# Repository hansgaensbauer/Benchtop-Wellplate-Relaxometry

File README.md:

# Benchtop Wellplate Relaxometry Hardware

Hardware for the system described in "Rapid Parallel Magnetic Resonance Relaxometry on Multiwell Plates with a Benchtop Scanner", by Hans Gaensbauer, Yanmeng Yang, Daniel Roxby, David Bono, and Jongyoon Han.

Also see the 96wp branch of [the MR-Core Repo](https://github.com/hansgaensbauer/MR-Core).

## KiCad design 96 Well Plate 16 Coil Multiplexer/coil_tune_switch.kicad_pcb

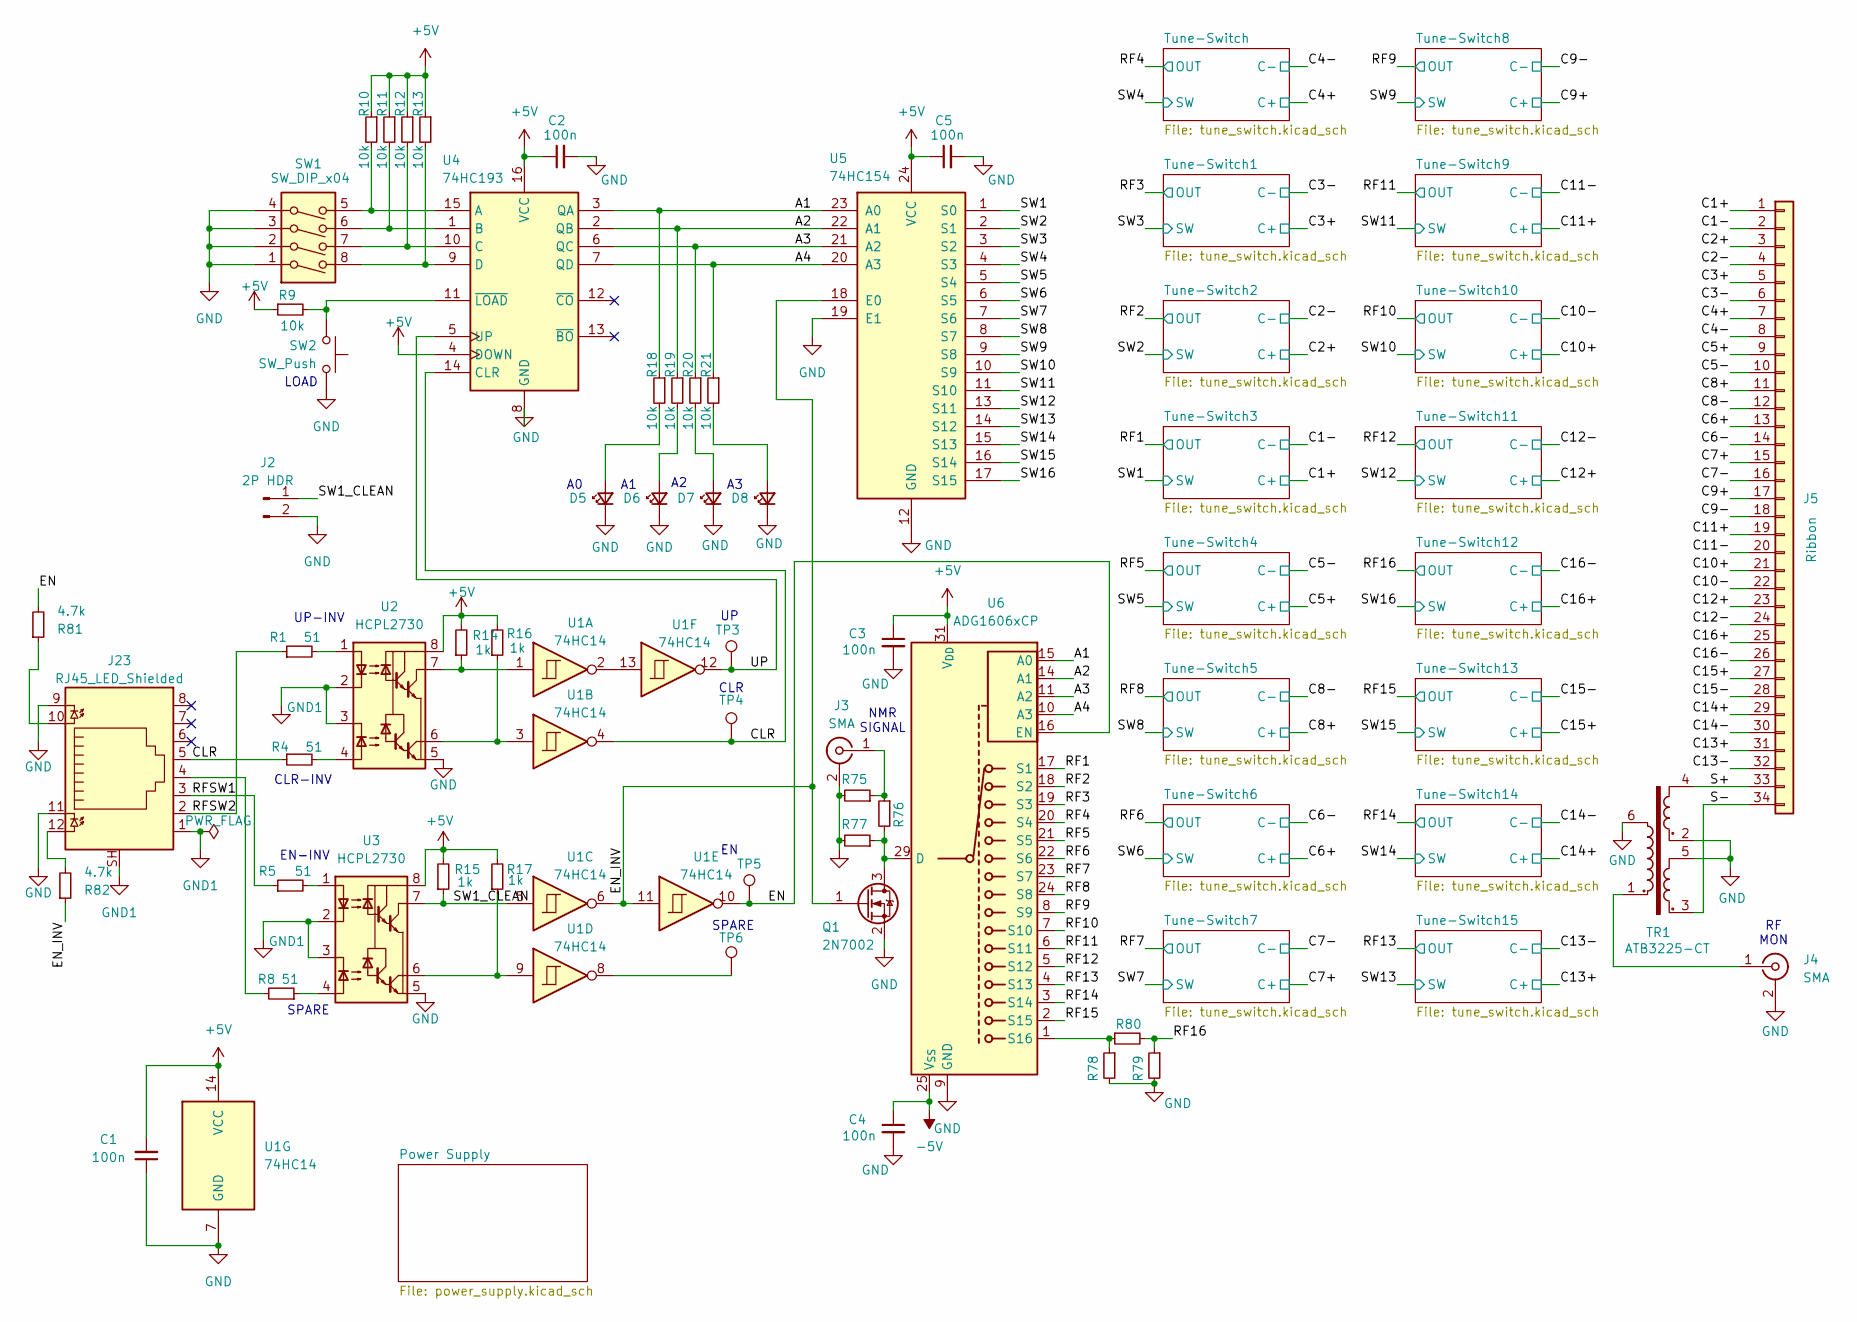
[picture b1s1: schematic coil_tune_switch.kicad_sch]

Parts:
C1, C2, C3, C4, C5: 100n; C_0603_1608Metric
D5, D6, D7, D8: LED_Small; LED_0603_1608Metric
J2: 2P HDR; PinHeader_1x02_P2.54mm_Vertical
J3, J4: SMA; SMA_Samtec_SMA-J-P-H-ST-EM1_EdgeMount
J5: Ribbon; IDC-Header_2x17_P2.54mm_Latch_Horizontal
J23: RJ45_LED_Shielded; RJ45_Amphenol_RJHSE538X
Q1: 2N7002; SOT-23
R1, R4, R5, R8: 51; R_0603_1608Metric
R9, R10, R11, R12, R13, R18, R19, R20, R21: 10k; R_0603_1608Metric
R14, R15, R16, R17, R75, R76, R77, R78, R79, R80: 1k; R_0603_1608Metric
R81, R82: 4.7k; R_0603_1608Metric
SW1: SW_DIP_x04; SW_DIP_SPSTx04_Slide_Omron_A6S-410x_W8.9mm_P2.54mm
SW2: SW_Push; SW_SPST_Omron_B3FS-100xP
TP3, TP4, TP5: TestPoint; TestPoint_Bridge_Pitch2.0mm_Drill0.7mm
TP6: TestPoint; TestPoint_THTPad_D1.0mm_Drill0.5mm
TR1: ATB3225-CT; ATB3225
U1: 74HC14; SOIC-14_3.9x8.7mm_P1.27mm
U2, U3: HCPL2730; SMDIP-8_W9.53mm
U4: 74HC193; SOIC-16_3.9x9.9mm_P1.27mm
U5: 74HC154; SOIC-24W_7.5x15.4mm_P1.27mm
U6: ADG1606xCP; LFCSP-32-1EP_5x5mm_P0.5mm_EP3.1x3.1mm

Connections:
+5V: C1.2, C2.1, C3.1, C5.1, R9.1, R10.1, R11.1, R12.1, R13.1, R14.2, R15.2, R16.2, R17.2, U1.14 (VCC), U2.8 (VCC), U3.8 (VCC), U4.4 (DOWN), U4.16 (VCC), U5.24 (VCC), U6.31 (V_{DD}); also elsewhere on the board
-5V: C4.1, U6.25 (V_{SS}), U6.33 (V_{SS}); also elsewhere on the board
/A1: R18.1, U4.3 (QA), U5.23 (A0), U6.15 (A0)
/A2: R19.1, U4.2 (QB), U5.22 (A1), U6.14 (A1)
/A3: R20.1, U4.6 (QC), U5.21 (A2), U6.11 (A2)
/A4: R21.1, U4.7 (QD), U5.20 (A3), U6.10 (A3)
/C1+: J5.1; also elsewhere on the board
/C1-: J5.2; also elsewhere on the board
/C2+: J5.3; also elsewhere on the board
/C2-: J5.4; also elsewhere on the board
/C3+: J5.5; also elsewhere on the board
/C3-: J5.6; also elsewhere on the board
/C4+: J5.7; also elsewhere on the board
/C4-: J5.8; also elsewhere on the board
/C5+: J5.9; also elsewhere on the board
/C5-: J5.10; also elsewhere on the board
/C6+: J5.13; also elsewhere on the board
/C6-: J5.14; also elsewhere on the board
/C7+: J5.15; also elsewhere on the board
/C7-: J5.16; also elsewhere on the board
/C8+: J5.11; also elsewhere on the board
/C8-: J5.12; also elsewhere on the board
/C9+: J5.17; also elsewhere on the board
/C9-: J5.18; also elsewhere on the board
/C10+: J5.21; also elsewhere on the board
/C10-: J5.22; also elsewhere on the board
/C11+: J5.19; also elsewhere on the board
/C11-: J5.20; also elsewhere on the board
/C12+: J5.23; also elsewhere on the board
/C12-: J5.24; also elsewhere on the board
/C13+: J5.31; also elsewhere on the board
/C13-: J5.32; also elsewhere on the board
/C14+: J5.29; also elsewhere on the board
/C14-: J5.30; also elsewhere on the board
/C15+: J5.27; also elsewhere on the board
/C15-: J5.28; also elsewhere on the board
/C16+: J5.25; also elsewhere on the board
/C16-: J5.26; also elsewhere on the board
/CLR: J23.5, R4.1, TP4.1, U1.4, U4.14 (CLR)
/EN: R81.2, TP5.1, U1.10, U6.16 (EN)
/EN_INV: Q1.1 (G), R82.1, U1.6, U1.11, U5.18 (E0)
/RF1: U6.17 (S1); also elsewhere on the board
/RF2: U6.18 (S2); also elsewhere on the board
/RF3: U6.19 (S3); also elsewhere on the board
/RF4: U6.20 (S4); also elsewhere on the board
/RF5: U6.21 (S5); also elsewhere on the board
/RF6: U6.22 (S6); also elsewhere on the board
/RF7: U6.23 (S7); also elsewhere on the board
/RF8: U6.24 (S8); also elsewhere on the board
/RF9: U6.8 (S9); also elsewhere on the board
/RF10: U6.7 (S10); also elsewhere on the board
/RF11: U6.6 (S11); also elsewhere on the board
/RF12: U6.5 (S12); also elsewhere on the board
/RF13: U6.4 (S13); also elsewhere on the board
/RF14: U6.3 (S14); also elsewhere on the board
/RF15: U6.2 (S15); also elsewhere on the board
/RF16: R79.1, R80.2; also elsewhere on the board
/RFSW1: J23.3, R5.1
/RFSW2: J23.2, R1.1
/S+: J5.33, TR1.4
/S-: J5.34, TR1.3
/SW1: U5.1 (S0); also elsewhere on the board
/SW1_CLEAN: J2.1, R15.1, U1.5, U3.7 (VO1)
/SW2: U5.2 (S1); also elsewhere on the board
/SW3: U5.3 (S2); also elsewhere on the board
/SW4: U5.4 (S3); also elsewhere on the board
/SW5: U5.5 (S4); also elsewhere on the board
/SW6: U5.6 (S5); also elsewhere on the board
/SW7: U5.7 (S6); also elsewhere on the board
/SW8: U5.8 (S7); also elsewhere on the board
/SW9: U5.9 (S8); also elsewhere on the board
/SW10: U5.10 (S9); also elsewhere on the board
/SW11: U5.11 (S10); also elsewhere on the board
/SW12: U5.13 (S11); also elsewhere on the board
/SW13: U5.14 (S12); also elsewhere on the board
/SW14: U5.15 (S13); also elsewhere on the board
/SW15: U5.16 (S14); also elsewhere on the board
/SW16: U5.17 (S15); also elsewhere on the board
/UP: TP3.1, U1.12, U4.5 (UP)
GND: C1.1, C2.2, C3.2, C4.2, C5.2, D5.1 (K), D6.1 (K), D7.1 (K), D8.1 (K), J2.2, J3.2 (Ext), J4.2 (Ext), J23.9, J23.11, Q1.2 (S), R75.2, R77.2, R78.2, R79.2, SW1.1, SW1.2, SW1.3, SW1.4, SW2.1, TR1.2, TR1.5, TR1.6, U1.7 (GND), U2.5 (GND), U3.5 (GND), U4.8 (GND), U5.12 (GND), U5.19 (E1), U6.9 (GND); also elsewhere on the board
GND1: J23.1, J23.SH, U2.2 (C1), U2.3 (C2), U3.2 (C1), U3.3 (C2)
unnamed: D5.2 (A), R18.2
unnamed: D6.2 (A), R19.2
unnamed: D7.2 (A), R20.2
unnamed: D8.2 (A), R21.2
unnamed: J3.1 (In), R75.1, R76.1
unnamed: J4.1 (In), TR1.1
unnamed: J23.4, R8.2
unnamed: J23.10, R81.1
unnamed: J23.12, R82.2
unnamed: Q1.3 (D), R76.2, R77.1, U6.29 (D)
unnamed: TP6.1, U1.8
unnamed: U1.2, U1.13
unnamed: R1.2, U2.1 (A1)
unnamed: R4.2, U2.4 (A2)
unnamed: R14.1, U1.1, U2.7 (VO1)
unnamed: R16.1, U1.3, U2.6 (VO2)
unnamed: R5.2, U3.1 (A1)
unnamed: R8.1, U3.4 (A2)
unnamed: R17.1, U1.9, U3.6 (VO2)
unnamed: R10.2, SW1.5, U4.15 (A)
unnamed: R11.2, SW1.6, U4.1 (B)
unnamed: R12.2, SW1.7, U4.10 (C)
unnamed: R13.2, SW1.8, U4.9 (D)
unnamed: R9.2, SW2.2, U4.11 (~LOAD)
unnamed: R78.1, R80.1, U6.1 (S16)

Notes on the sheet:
UP-INV
NMR SIGNAL
RF MON
CLR-INV
EN-INV
SPARE
CLR
LOAD

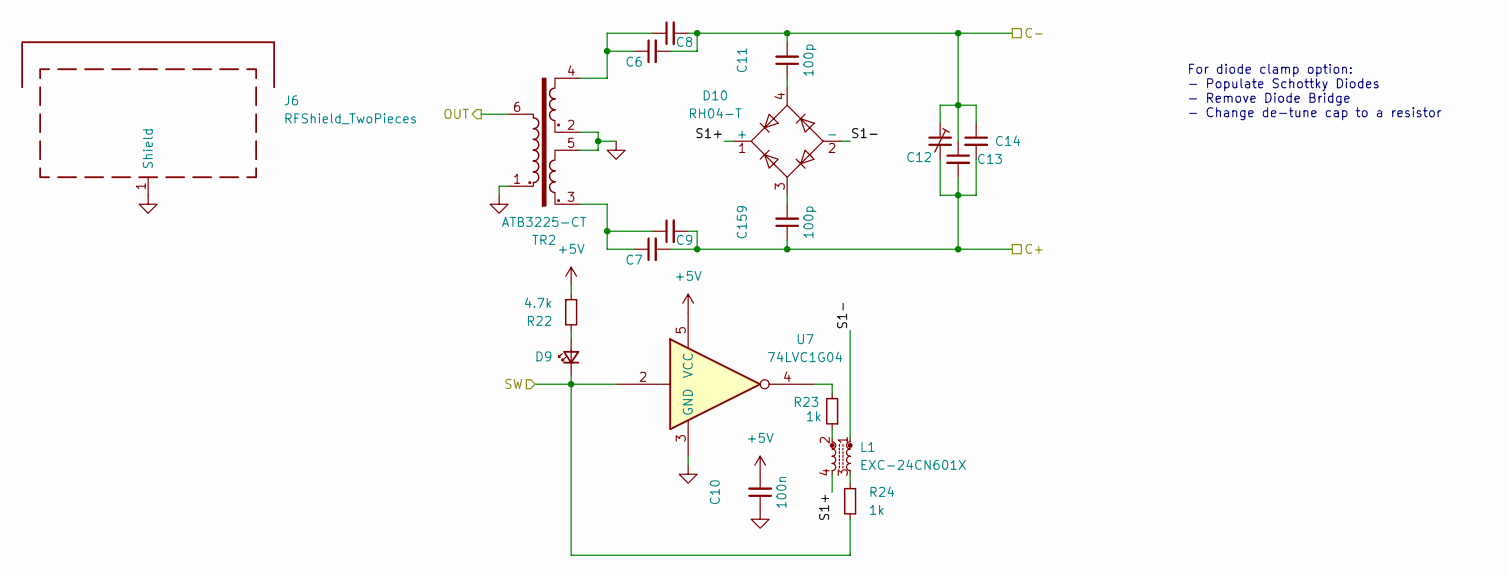
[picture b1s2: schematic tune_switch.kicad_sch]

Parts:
C6, C7, C8, C9, C13, C14: C_Small; C_0603_1608Metric
C10: 100n; C_0603_1608Metric
C11, C159: 100p; C_0603_1608Metric
C12: C_Trim_Small; C_Trimmer_Voltronics_JZ
D9: LED_Small; LED_0603_1608Metric
D10: RH04-T; MiniDIP-4
J6: RFShield_TwoPieces; Laird_Technologies_BMI-S-202-F_16.50x16.50mm
L1: EXC-24CN601X
R22: 4.7k; R_0603_1608Metric
R23, R24: 1k; R_0603_1608Metric
TR2: ATB3225-CT; ATB3225
U7: 74LVC1G04; SOT-353_SC-70-5

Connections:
+5V: C10.2, R22.1, U7.5 (VCC); also elsewhere on the board
/C4+: C7.2, C9.2, C12.2, C13.2, C14.2, C159.1; also elsewhere on the board
/C4-: C6.2, C8.2, C11.2, C12.1, C13.1, C14.1; also elsewhere on the board
/RF4: TR2.6; also elsewhere on the board
/SW4: D9.1 (K), R24.1, U7.2; also elsewhere on the board
/Tune-Switch/S1+: D10.1 (+), L1.4
/Tune-Switch/S1-: D10.2 (-), L1.1
GND: C10.1, J6.1 (Shield), TR2.1, TR2.2, TR2.5, U7.3 (GND); also elsewhere on the board
unnamed: C6.1, C8.1, TR2.4
unnamed: C7.1, C9.1, TR2.3
unnamed: C11.1, D10.4
unnamed: C159.2, D10.3
unnamed: D9.2 (A), R22.2
unnamed: L1.2, R23.1
unnamed: L1.3, R24.2
unnamed: R23.2, U7.4

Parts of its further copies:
C15, C16, C17, C18, C22, C23, C24, C25, C26, C27, C31, C32, C33, C34, C35, C36, C40, C41, C42, C43, C44, C45, C49, C50, C51, C52, C53, C54, C58, C59, C60, C61, C62, C63, C67, C68, C69, C70, C71, C72, C76, C77, C78, C79, C80, C81, C85, C86, C87, C88, C89, C90, C94, C95, C96, C97, C98, C99, C103, C104, C105, C106, C107, C108, C112, C113, C114, C115, C116, C117, C121, C122, C123, C124, C125, C126, C130, C131, C132, C133, C134, C135, C139, C140, C141, C142, C143, C144, C148, C149: C_Small; C_0603_1608Metric
C19, C28, C37, C46, C55, C64, C73, C82, C91, C100, C109, C118, C127, C136, C145: 100n; C_0603_1608Metric
C20, C29, C38, C47, C56, C65, C74, C83, C92, C101, C110, C119, C128, C137, C146, C160, C161, C162, C163, C164, C165, C166, C167, C168, C169, C170, C171, C172, C173, C174: 100p; C_0603_1608Metric
C21, C30, C39, C48, C57, C66, C75, C84, C93, C102, C111, C120, C129, C138, C147: C_Trim_Small; C_Trimmer_Voltronics_JZ
D13, D17, D21, D25, D29, D33, D37, D41, D45, D49, D53, D57, D61, D65, D69: LED_Small; LED_0603_1608Metric
D14, D18, D22, D26, D30, D34, D38, D42, D46, D50, D54, D58, D62, D66, D70: RH04-T; MiniDIP-4
J7, J8, J9, J10, J11, J12, J13, J14, J15, J16, J17, J18, J19, J20, J21: RFShield_TwoPieces; Laird_Technologies_BMI-S-202-F_16.50x16.50mm
L2, L3, L4, L5, L6, L7, L8, L9, L10, L11, L12, L13, L14, L15, L16: EXC-24CN601X
R25, R28, R31, R34, R37, R40, R43, R46, R49, R52, R55, R58, R61, R64, R67: 4.7k; R_0603_1608Metric
R26, R27, R29, R30, R32, R33, R35, R36, R38, R39, R41, R42, R44, R45, R47, R48, R50, R51, R53, R54, R56, R57, R59, R60, R62, R63, R65, R66, R68, R69: 1k; R_0603_1608Metric
TR3, TR4, TR5, TR6, TR7, TR8, TR9, TR10, TR11, TR12, TR13, TR14, TR15, TR16, TR17: ATB3225-CT; ATB3225
U8, U9, U10, U11, U12, U13, U14, U15, U16, U17, U18, U19, U20, U21, U22: 74LVC1G04; SOT-353_SC-70-5

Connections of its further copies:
+5V: C19.2, C28.2, C37.2, C46.2, C55.2, C64.2, C73.2, C82.2, C91.2, C100.2, C109.2, C118.2, C127.2, C136.2, C145.2, R25.1, R28.1, R31.1, R34.1, R37.1, R40.1, R43.1, R46.1, R49.1, R52.1, R55.1, R58.1, R61.1, R64.1, R67.1, U8.5 (VCC), U9.5 (VCC), U10.5 (VCC), U11.5 (VCC), U12.5 (VCC), U13.5 (VCC), U14.5 (VCC), U15.5 (VCC), U16.5 (VCC), U17.5 (VCC), U18.5 (VCC), U19.5 (VCC), U20.5 (VCC), U21.5 (VCC), U22.5 (VCC); also elsewhere on the board
/C1+: C34.2, C36.2, C39.2, C40.2, C41.2, C162.1; also elsewhere on the board
/C1-: C33.2, C35.2, C38.2, C39.1, C40.1, C41.1; also elsewhere on the board
/C2+: C25.2, C27.2, C30.2, C31.2, C32.2, C161.1; also elsewhere on the board
/C2-: C24.2, C26.2, C29.2, C30.1, C31.1, C32.1; also elsewhere on the board
/C3+: C16.2, C18.2, C21.2, C22.2, C23.2, C160.1; also elsewhere on the board
/C3-: C15.2, C17.2, C20.2, C21.1, C22.1, C23.1; also elsewhere on the board
/C5+: C43.2, C45.2, C48.2, C49.2, C50.2, C163.1; also elsewhere on the board
/C5-: C42.2, C44.2, C47.2, C48.1, C49.1, C50.1; also elsewhere on the board
/C6+: C61.2, C63.2, C66.2, C67.2, C68.2, C165.1; also elsewhere on the board
/C6-: C60.2, C62.2, C65.2, C66.1, C67.1, C68.1; also elsewhere on the board
/C7+: C70.2, C72.2, C75.2, C76.2, C77.2, C166.1; also elsewhere on the board
/C7-: C69.2, C71.2, C74.2, C75.1, C76.1, C77.1; also elsewhere on the board
/C8+: C52.2, C54.2, C57.2, C58.2, C59.2, C164.1; also elsewhere on the board
/C8-: C51.2, C53.2, C56.2, C57.1, C58.1, C59.1; also elsewhere on the board
/C9+: C79.2, C81.2, C84.2, C85.2, C86.2, C167.1; also elsewhere on the board
/C9-: C78.2, C80.2, C83.2, C84.1, C85.1, C86.1; also elsewhere on the board
/C10+: C97.2, C99.2, C102.2, C103.2, C104.2, C169.1; also elsewhere on the board
/C10-: C96.2, C98.2, C101.2, C102.1, C103.1, C104.1; also elsewhere on the board
/C11+: C88.2, C90.2, C93.2, C94.2, C95.2, C168.1; also elsewhere on the board
/C11-: C87.2, C89.2, C92.2, C93.1, C94.1, C95.1; also elsewhere on the board
/C12+: C106.2, C108.2, C111.2, C112.2, C113.2, C170.1; also elsewhere on the board
/C12-: C105.2, C107.2, C110.2, C111.1, C112.1, C113.1; also elsewhere on the board
/C13+: C142.2, C144.2, C147.2, C148.2, C149.2, C174.1; also elsewhere on the board
/C13-: C141.2, C143.2, C146.2, C147.1, C148.1, C149.1; also elsewhere on the board
/C14+: C133.2, C135.2, C138.2, C139.2, C140.2, C173.1; also elsewhere on the board
/C14-: C132.2, C134.2, C137.2, C138.1, C139.1, C140.1; also elsewhere on the board
/C15+: C124.2, C126.2, C129.2, C130.2, C131.2, C172.1; also elsewhere on the board
/C15-: C123.2, C125.2, C128.2, C129.1, C130.1, C131.1; also elsewhere on the board
/C16+: C115.2, C117.2, C120.2, C121.2, C122.2, C171.1; also elsewhere on the board
/C16-: C114.2, C116.2, C119.2, C120.1, C121.1, C122.1; also elsewhere on the board
/RF1: TR5.6; also elsewhere on the board
/RF2: TR4.6; also elsewhere on the board
/RF3: TR3.6; also elsewhere on the board
/RF5: TR6.6; also elsewhere on the board
/RF6: TR8.6; also elsewhere on the board
/RF7: TR9.6; also elsewhere on the board
/RF8: TR7.6; also elsewhere on the board
/RF9: TR10.6; also elsewhere on the board
/RF10: TR12.6; also elsewhere on the board
/RF11: TR11.6; also elsewhere on the board
/RF12: TR13.6; also elsewhere on the board
/RF13: TR17.6; also elsewhere on the board
/RF14: TR16.6; also elsewhere on the board
/RF15: TR15.6; also elsewhere on the board
/RF16: TR14.6; also elsewhere on the board
/SW1: D21.1 (K), R33.1, U10.2; also elsewhere on the board
/SW2: D17.1 (K), R30.1, U9.2; also elsewhere on the board
/SW3: D13.1 (K), R27.1, U8.2; also elsewhere on the board
/SW5: D25.1 (K), R36.1, U11.2; also elsewhere on the board
/SW6: D33.1 (K), R42.1, U13.2; also elsewhere on the board
/SW7: D37.1 (K), R45.1, U14.2; also elsewhere on the board
/SW8: D29.1 (K), R39.1, U12.2; also elsewhere on the board
/SW9: D41.1 (K), R48.1, U15.2; also elsewhere on the board
/SW10: D49.1 (K), R54.1, U17.2; also elsewhere on the board
/SW11: D45.1 (K), R51.1, U16.2; also elsewhere on the board
/SW12: D53.1 (K), R57.1, U18.2; also elsewhere on the board
/SW13: D69.1 (K), R69.1, U22.2; also elsewhere on the board
/SW14: D65.1 (K), R66.1, U21.2; also elsewhere on the board
/SW15: D61.1 (K), R63.1, U20.2; also elsewhere on the board
/SW16: D57.1 (K), R60.1, U19.2; also elsewhere on the board
/Tune-Switch1/S1+: D14.1 (+), L2.4
/Tune-Switch1/S1-: D14.2 (-), L2.1
/Tune-Switch2/S1+: D18.1 (+), L3.4
/Tune-Switch2/S1-: D18.2 (-), L3.1
/Tune-Switch3/S1+: D22.1 (+), L4.4
/Tune-Switch3/S1-: D22.2 (-), L4.1
/Tune-Switch4/S1+: D26.1 (+), L5.4
/Tune-Switch4/S1-: D26.2 (-), L5.1
/Tune-Switch5/S1+: D30.1 (+), L6.4
/Tune-Switch5/S1-: D30.2 (-), L6.1
/Tune-Switch6/S1+: D34.1 (+), L7.4
/Tune-Switch6/S1-: D34.2 (-), L7.1
/Tune-Switch7/S1+: D38.1 (+), L8.4
/Tune-Switch7/S1-: D38.2 (-), L8.1
/Tune-Switch8/S1+: D42.1 (+), L9.4
/Tune-Switch8/S1-: D42.2 (-), L9.1
/Tune-Switch9/S1+: D46.1 (+), L10.4
/Tune-Switch9/S1-: D46.2 (-), L10.1
/Tune-Switch10/S1+: D50.1 (+), L11.4
/Tune-Switch10/S1-: D50.2 (-), L11.1
/Tune-Switch11/S1+: D54.1 (+), L12.4
/Tune-Switch11/S1-: D54.2 (-), L12.1
/Tune-Switch12/S1+: D58.1 (+), L13.4
/Tune-Switch12/S1-: D58.2 (-), L13.1
/Tune-Switch13/S1+: D62.1 (+), L14.4
/Tune-Switch13/S1-: D62.2 (-), L14.1
/Tune-Switch14/S1+: D66.1 (+), L15.4
/Tune-Switch14/S1-: D66.2 (-), L15.1
/Tune-Switch15/S1+: D70.1 (+), L16.4
/Tune-Switch15/S1-: D70.2 (-), L16.1
GND: C19.1, C28.1, C37.1, C46.1, C55.1, C64.1, C73.1, C82.1, C91.1, C100.1, C109.1, C118.1, C127.1, C136.1, C145.1, J7.1 (Shield), J8.1 (Shield), J9.1 (Shield), J10.1 (Shield), J11.1 (Shield), J12.1 (Shield), J13.1 (Shield), J14.1 (Shield), J15.1 (Shield), J16.1 (Shield), J17.1 (Shield), J18.1 (Shield), J19.1 (Shield), J20.1 (Shield), J21.1 (Shield), TR3.1, TR3.2, TR3.5, TR4.1, TR4.2, TR4.5, TR5.1, TR5.2, TR5.5, TR6.1, TR6.2, TR6.5, TR7.1, TR7.2, TR7.5, TR8.1, TR8.2, TR8.5, TR9.1, TR9.2, TR9.5, TR10.1, TR10.2, TR10.5, TR11.1, TR11.2, TR11.5, TR12.1, TR12.2, TR12.5, TR13.1, TR13.2, TR13.5, TR14.1, TR14.2, TR14.5, TR15.1, TR15.2, TR15.5, TR16.1, TR16.2, TR16.5, TR17.1, TR17.2, TR17.5, U8.3 (GND), U9.3 (GND), U10.3 (GND), U11.3 (GND), U12.3 (GND), U13.3 (GND), U14.3 (GND), U15.3 (GND), U16.3 (GND), U17.3 (GND), U18.3 (GND), U19.3 (GND), U20.3 (GND), U21.3 (GND), U22.3 (GND); also elsewhere on the board
unnamed: C15.1, C17.1, TR3.4
unnamed: C16.1, C18.1, TR3.3
unnamed: C20.1, D14.4
unnamed: C24.1, C26.1, TR4.4
unnamed: C25.1, C27.1, TR4.3
unnamed: C29.1, D18.4
unnamed: C33.1, C35.1, TR5.4
unnamed: C34.1, C36.1, TR5.3
unnamed: C38.1, D22.4
unnamed: C42.1, C44.1, TR6.4
unnamed: C43.1, C45.1, TR6.3
unnamed: C47.1, D26.4
unnamed: C51.1, C53.1, TR7.4
unnamed: C52.1, C54.1, TR7.3
unnamed: C56.1, D30.4
unnamed: C60.1, C62.1, TR8.4
unnamed: C61.1, C63.1, TR8.3
unnamed: C65.1, D34.4
unnamed: C69.1, C71.1, TR9.4
unnamed: C70.1, C72.1, TR9.3
unnamed: C74.1, D38.4
unnamed: C78.1, C80.1, TR10.4
unnamed: C79.1, C81.1, TR10.3
unnamed: C83.1, D42.4
unnamed: C87.1, C89.1, TR11.4
unnamed: C88.1, C90.1, TR11.3
unnamed: C92.1, D46.4
unnamed: C96.1, C98.1, TR12.4
unnamed: C97.1, C99.1, TR12.3
unnamed: C101.1, D50.4
unnamed: C105.1, C107.1, TR13.4
unnamed: C106.1, C108.1, TR13.3
unnamed: C110.1, D54.4
unnamed: C114.1, C116.1, TR14.4
unnamed: C115.1, C117.1, TR14.3
unnamed: C119.1, D58.4
unnamed: C123.1, C125.1, TR15.4
unnamed: C124.1, C126.1, TR15.3
unnamed: C128.1, D62.4
unnamed: C132.1, C134.1, TR16.4
unnamed: C133.1, C135.1, TR16.3
unnamed: C137.1, D66.4
unnamed: C141.1, C143.1, TR17.4
unnamed: C142.1, C144.1, TR17.3
unnamed: C146.1, D70.4
unnamed: C160.2, D14.3
unnamed: C161.2, D18.3
unnamed: C162.2, D22.3
unnamed: C163.2, D26.3
unnamed: C164.2, D30.3
unnamed: C165.2, D34.3
unnamed: C166.2, D38.3
unnamed: C167.2, D42.3
unnamed: C168.2, D46.3
unnamed: C169.2, D50.3
unnamed: C170.2, D54.3
unnamed: C171.2, D58.3
unnamed: C172.2, D62.3
unnamed: C173.2, D66.3
unnamed: C174.2, D70.3
unnamed: D13.2 (A), R25.2
unnamed: D17.2 (A), R28.2
unnamed: D21.2 (A), R31.2
unnamed: D25.2 (A), R34.2
unnamed: D29.2 (A), R37.2
unnamed: D33.2 (A), R40.2
unnamed: D37.2 (A), R43.2
unnamed: D41.2 (A), R46.2
unnamed: D45.2 (A), R49.2
unnamed: D49.2 (A), R52.2
unnamed: D53.2 (A), R55.2
unnamed: D57.2 (A), R58.2
unnamed: D61.2 (A), R61.2
unnamed: D65.2 (A), R64.2
unnamed: D69.2 (A), R67.2
unnamed: L2.2, R26.1
unnamed: L2.3, R27.2
unnamed: L3.2, R29.1
unnamed: L3.3, R30.2
unnamed: L4.2, R32.1
unnamed: L4.3, R33.2
unnamed: L5.2, R35.1
unnamed: L5.3, R36.2
unnamed: L6.2, R38.1
unnamed: L6.3, R39.2
unnamed: L7.2, R41.1
unnamed: L7.3, R42.2
unnamed: L8.2, R44.1
unnamed: L8.3, R45.2
unnamed: L9.2, R47.1
unnamed: L9.3, R48.2
unnamed: L10.2, R50.1
unnamed: L10.3, R51.2
unnamed: L11.2, R53.1
unnamed: L11.3, R54.2
unnamed: L12.2, R56.1
unnamed: L12.3, R57.2
unnamed: L13.2, R59.1
unnamed: L13.3, R60.2
unnamed: L14.2, R62.1
unnamed: L14.3, R63.2
unnamed: L15.2, R65.1
unnamed: L15.3, R66.2
unnamed: L16.2, R68.1
unnamed: L16.3, R69.2
unnamed: R26.2, U8.4
unnamed: R29.2, U9.4
unnamed: R32.2, U10.4
unnamed: R35.2, U11.4
unnamed: R38.2, U12.4
unnamed: R41.2, U13.4
unnamed: R44.2, U14.4
unnamed: R47.2, U15.4
unnamed: R50.2, U16.4
unnamed: R53.2, U17.4
unnamed: R56.2, U18.4
unnamed: R59.2, U19.4
unnamed: R62.2, U20.4
unnamed: R65.2, U21.4
unnamed: R68.2, U22.4

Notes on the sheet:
For diode clamp option: - Populate Schottky Diodes - Remove Diode Bridge - Change de-tune cap to a resistor

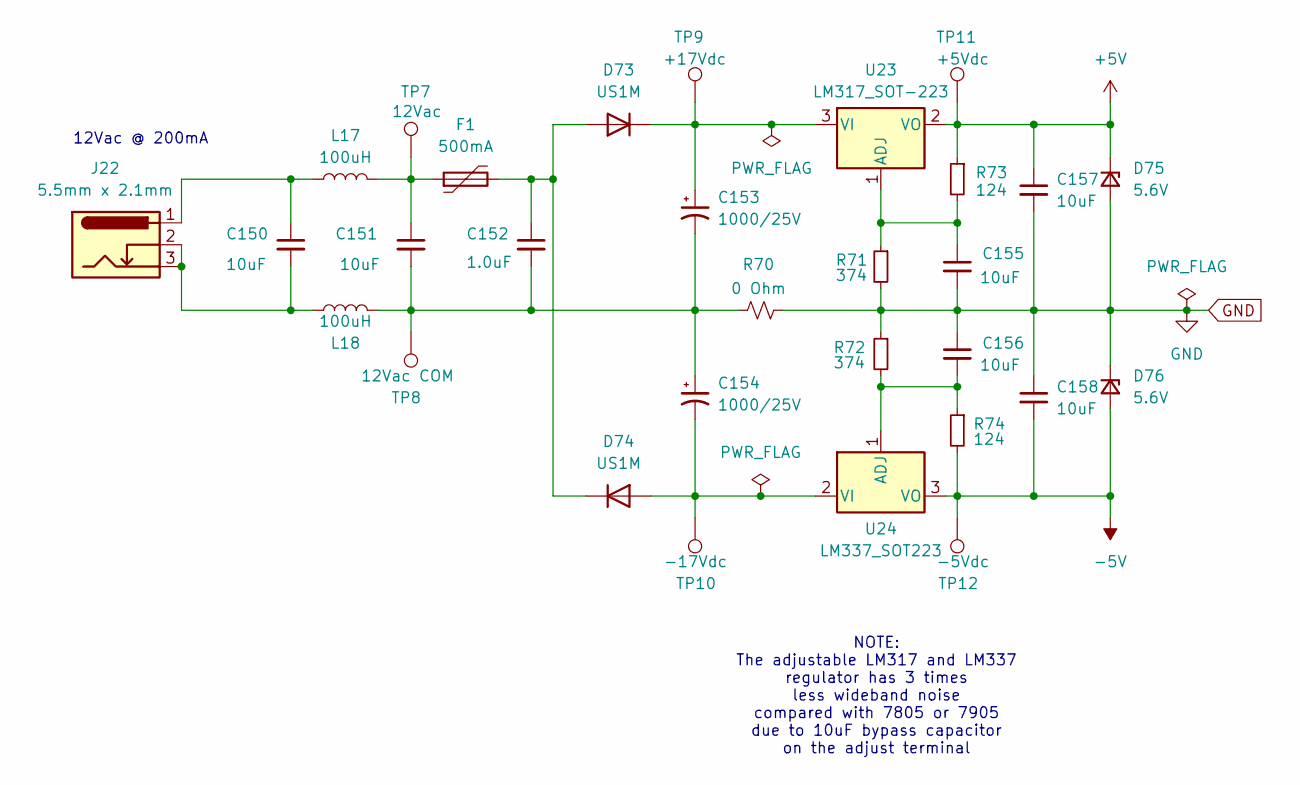
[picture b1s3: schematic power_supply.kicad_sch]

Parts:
C150, C151: 10uF; C_1206_3216Metric_Pad1.33x1.80mm_HandSolder
C152: 1.0uF; C_1206_3216Metric_Pad1.33x1.80mm_HandSolder
C153, C154: 1000/25V; CP_Radial_D16.0mm_P7.50mm
C155, C156, C157, C158: 10uF; C_1206_3216Metric
D73, D74: US1M; D_SMA
D75, D76: 5.6V; D_SMC_Handsoldering
F1: 500mA; Fuse_1210_3225Metric_Pad1.42x2.65mm_HandSolder
J22: 5.5mm x 2.1mm; BarrelJack_CUI_PJ-102AH_Horizontal
L17, L18: 100uH; L_1812_4532Metric_Pad1.30x3.40mm_HandSolder
R70: 0 Ohm; R_0603_1608Metric
R71, R72: 374; R_0603_1608Metric
R73, R74: 124; R_0603_1608Metric
TP7: 12Vac; TestPoint_Bridge_Pitch2.0mm_Drill0.7mm
TP8: 12Vac COM; TestPoint_Bridge_Pitch2.0mm_Drill0.7mm
TP9: +17Vdc; TestPoint_Bridge_Pitch2.0mm_Drill0.7mm
TP10: -17Vdc; TestPoint_Bridge_Pitch2.0mm_Drill0.7mm
TP11: +5Vdc; TestPoint_Bridge_Pitch2.0mm_Drill0.7mm
TP12: -5Vdc; TestPoint_Bridge_Pitch2.0mm_Drill0.7mm
U23: LM317_SOT-223; SOT-223-3_TabPin2
U24: LM337_SOT223; SOT-223-3_TabPin2

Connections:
+5V: C157.1, D75.1 (K), R73.1, TP11.1, U23.2 (VO); also elsewhere on the board
-5V: C158.2, D76.2 (A), R74.2, TP12.1, U24.3 (VO); also elsewhere on the board
GND: C155.2, C156.1, C157.2, C158.1, D75.2 (A), D76.1 (K), R70.2, R71.2, R72.1; also elsewhere on the board
unnamed: C150.1, J22.1, L17.1
unnamed: C150.2, J22.2, J22.3, L18.1
unnamed: C151.1, F1.1, L17.2, TP7.1
unnamed: C151.2, C152.2, C153.2, C154.1, L18.2, R70.1, TP8.1
unnamed: C152.1, D73.2 (A), D74.1 (K), F1.2
unnamed: C153.1, D73.1 (K), TP9.1, U23.3 (VI)
unnamed: C154.2, D74.2 (A), TP10.1, U24.2 (VI)
unnamed: C155.1, R71.1, R73.2, U23.1 (ADJ)
unnamed: C156.2, R72.2, R74.1, U24.1 (ADJ)

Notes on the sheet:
NOTE: The adjustable LM317 and LM337 regulator has 3 times less wideband noise compared with 7805 or 7905 due to 10uF bypass capacitor on the adjust terminal
12Vac @ 200mA

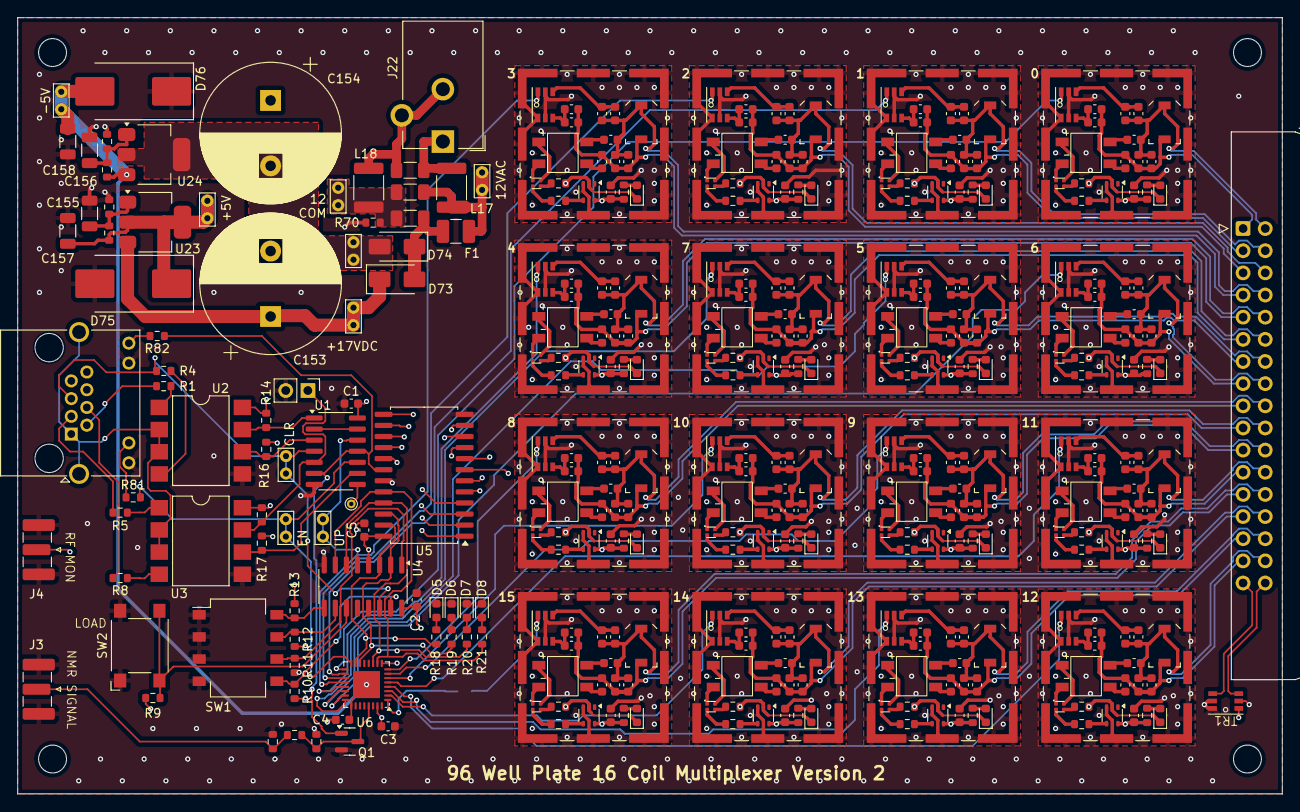
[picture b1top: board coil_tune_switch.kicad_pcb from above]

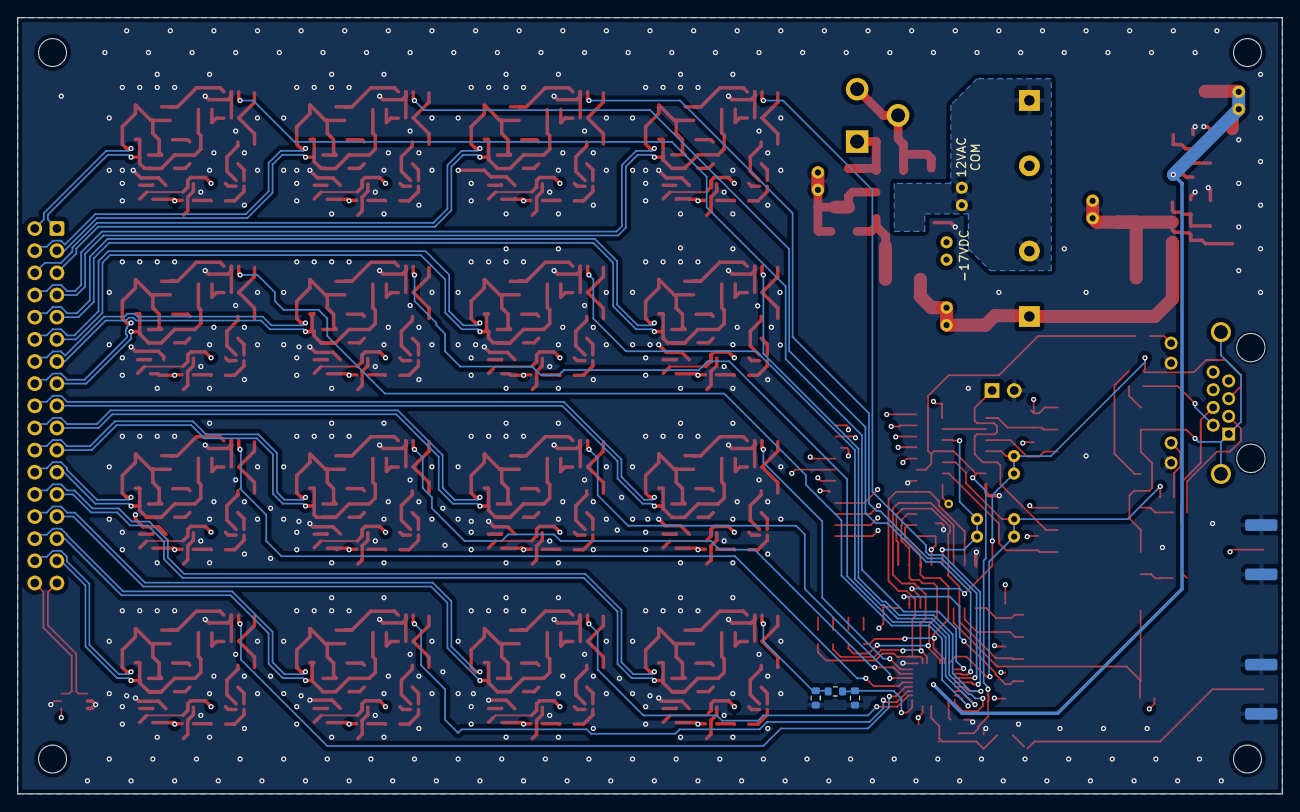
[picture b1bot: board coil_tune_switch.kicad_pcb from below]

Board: 4 copper layers, 145.0 x 89.0 mm, 387 parts (3 on the bottom side), 275 nets.

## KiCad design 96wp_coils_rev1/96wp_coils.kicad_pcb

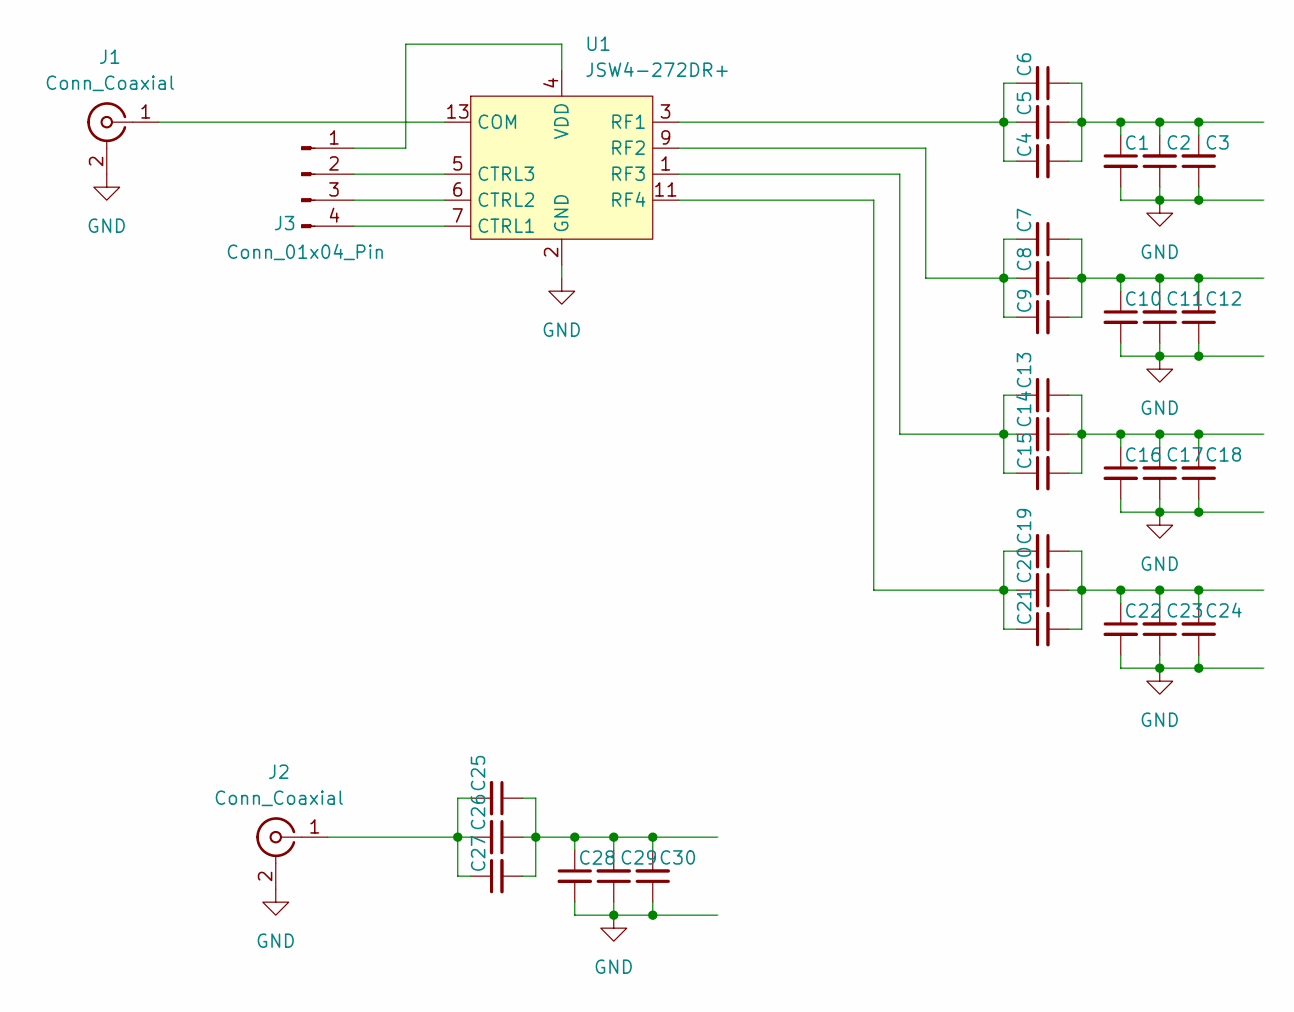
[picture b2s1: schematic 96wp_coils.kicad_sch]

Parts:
C1, C2, C3, C4, C5, C6, C7, C8, C9, C10, C11, C12, C13, C14, C15, C16, C17, C18, C19, C20, C21, C22, C23, C24, C25, C26, C27, C28, C29, C30: C_Small; C_0603_1608Metric
J1, J2: Conn_Coaxial; SMA_Samtec_SMA-J-P-X-ST-EM1_EdgeMount
J3: Conn_01x04_Pin; PinHeader_1x04_P2.54mm_Vertical
U1: JSW4-272DR+; MT1817

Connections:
GND: C1.2, C2.1, C3.1, C10.2, C11.1, C12.1, C16.2, C17.1, C18.1, C22.2, C23.1, C24.1, C28.2, C29.1, C30.1, J1.2 (Ext), J2.2 (Ext), U1.2 (GND), U1.10 (GND), U1.15 (GND)
unnamed: C1.1, C2.2, C3.2, C4.2, C5.1, C6.1
unnamed: C7.1, C8.1, C9.2, C10.1, C11.2, C12.2
unnamed: C13.1, C14.1, C15.2, C16.1, C17.2, C18.2
unnamed: C19.1, C20.1, C21.2, C22.1, C23.2, C24.2
unnamed: C25.1, C26.1, C27.2, C28.1, C29.2, C30.2
unnamed: J1.1 (In), U1.13 (COM)
unnamed: C25.2, C26.2, C27.1, J2.1 (In)
unnamed: J3.1, U1.4 (VDD)
unnamed: J3.2, U1.5 (CTRL3)
unnamed: J3.3, U1.6 (CTRL2)
unnamed: J3.4, U1.7 (CTRL1)
unnamed: C4.1, C5.2, C6.2, U1.3 (RF1)
unnamed: C7.2, C8.2, C9.1, U1.9 (RF2)
unnamed: C13.2, C14.2, C15.1, U1.1 (RF3)
unnamed: C19.2, C20.2, C21.1, U1.11 (RF4)

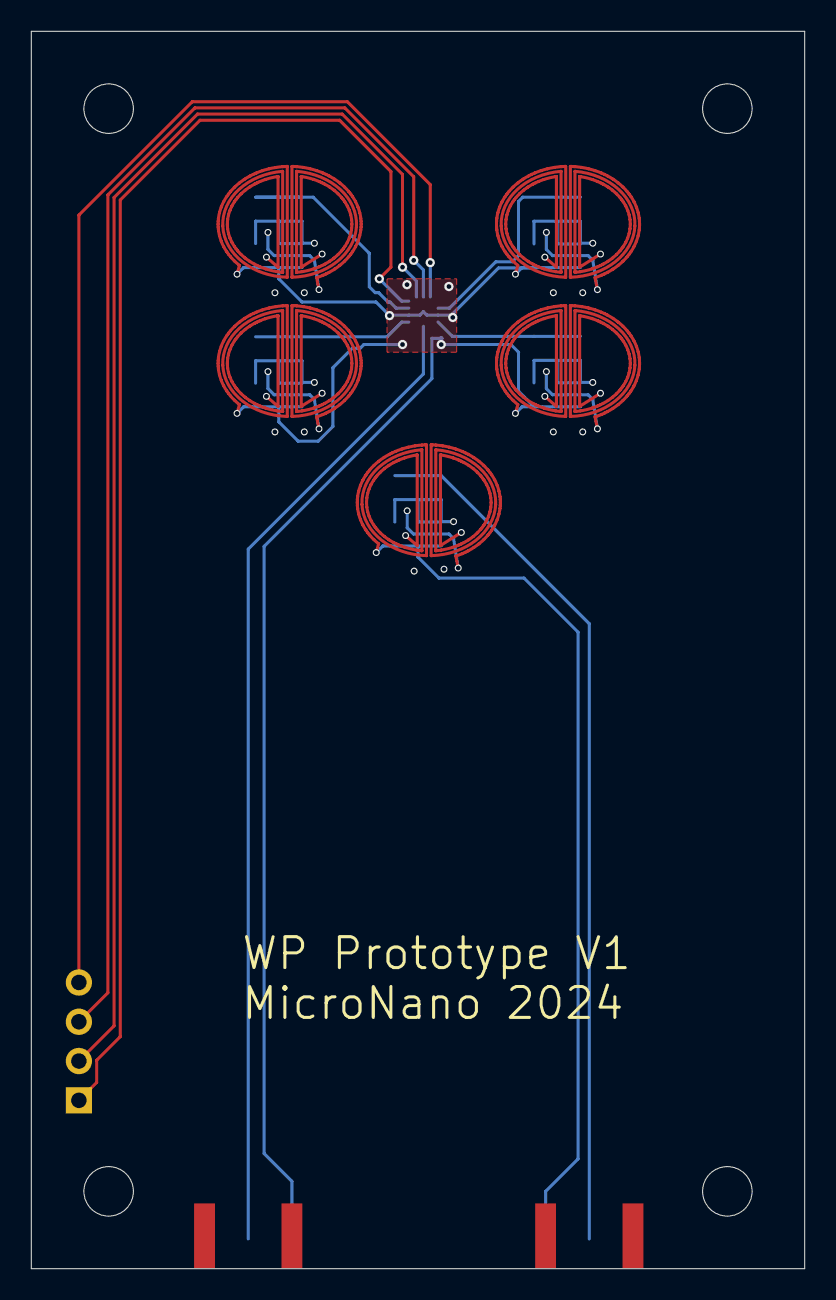
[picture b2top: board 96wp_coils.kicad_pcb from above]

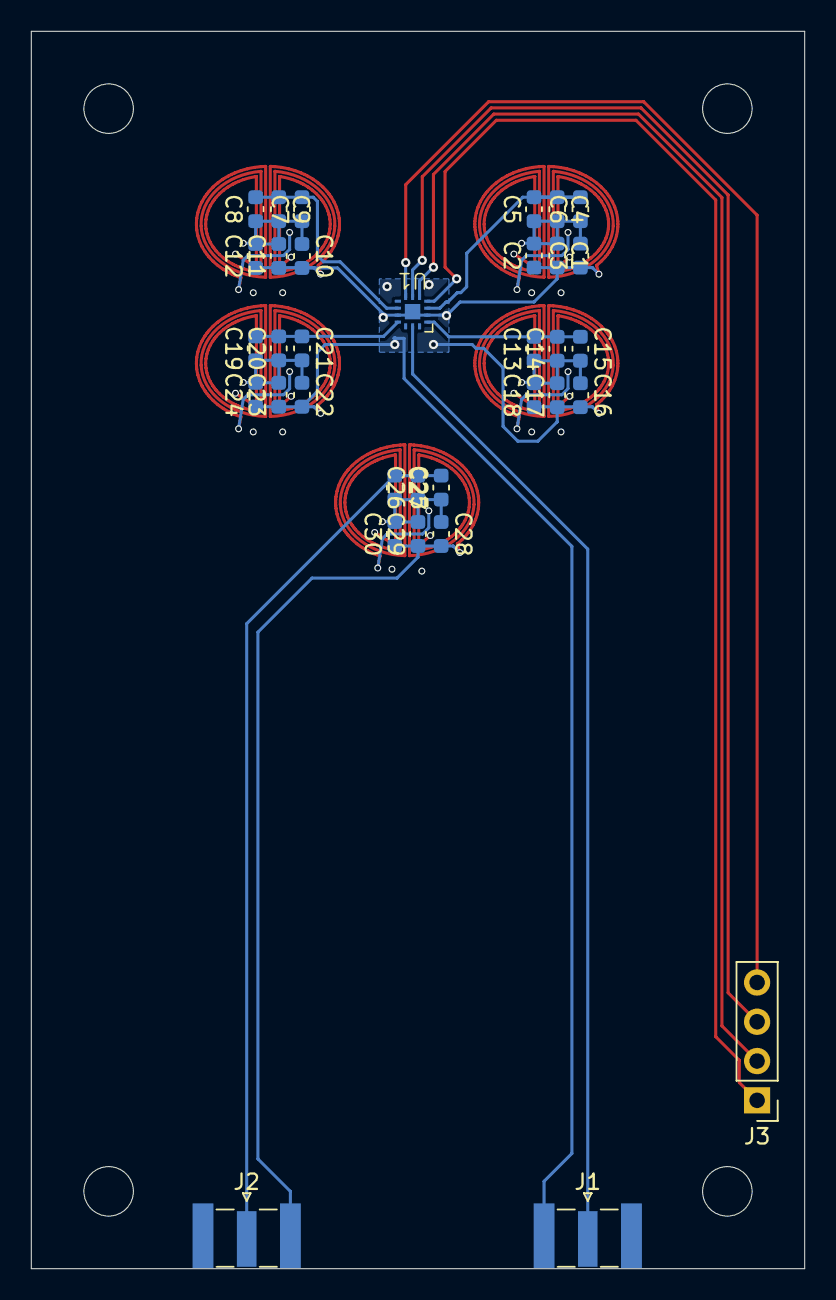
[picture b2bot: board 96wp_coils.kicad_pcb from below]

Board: 4 copper layers, 50.0 x 80.0 mm, 34 parts (34 on the bottom side), 16 nets.
